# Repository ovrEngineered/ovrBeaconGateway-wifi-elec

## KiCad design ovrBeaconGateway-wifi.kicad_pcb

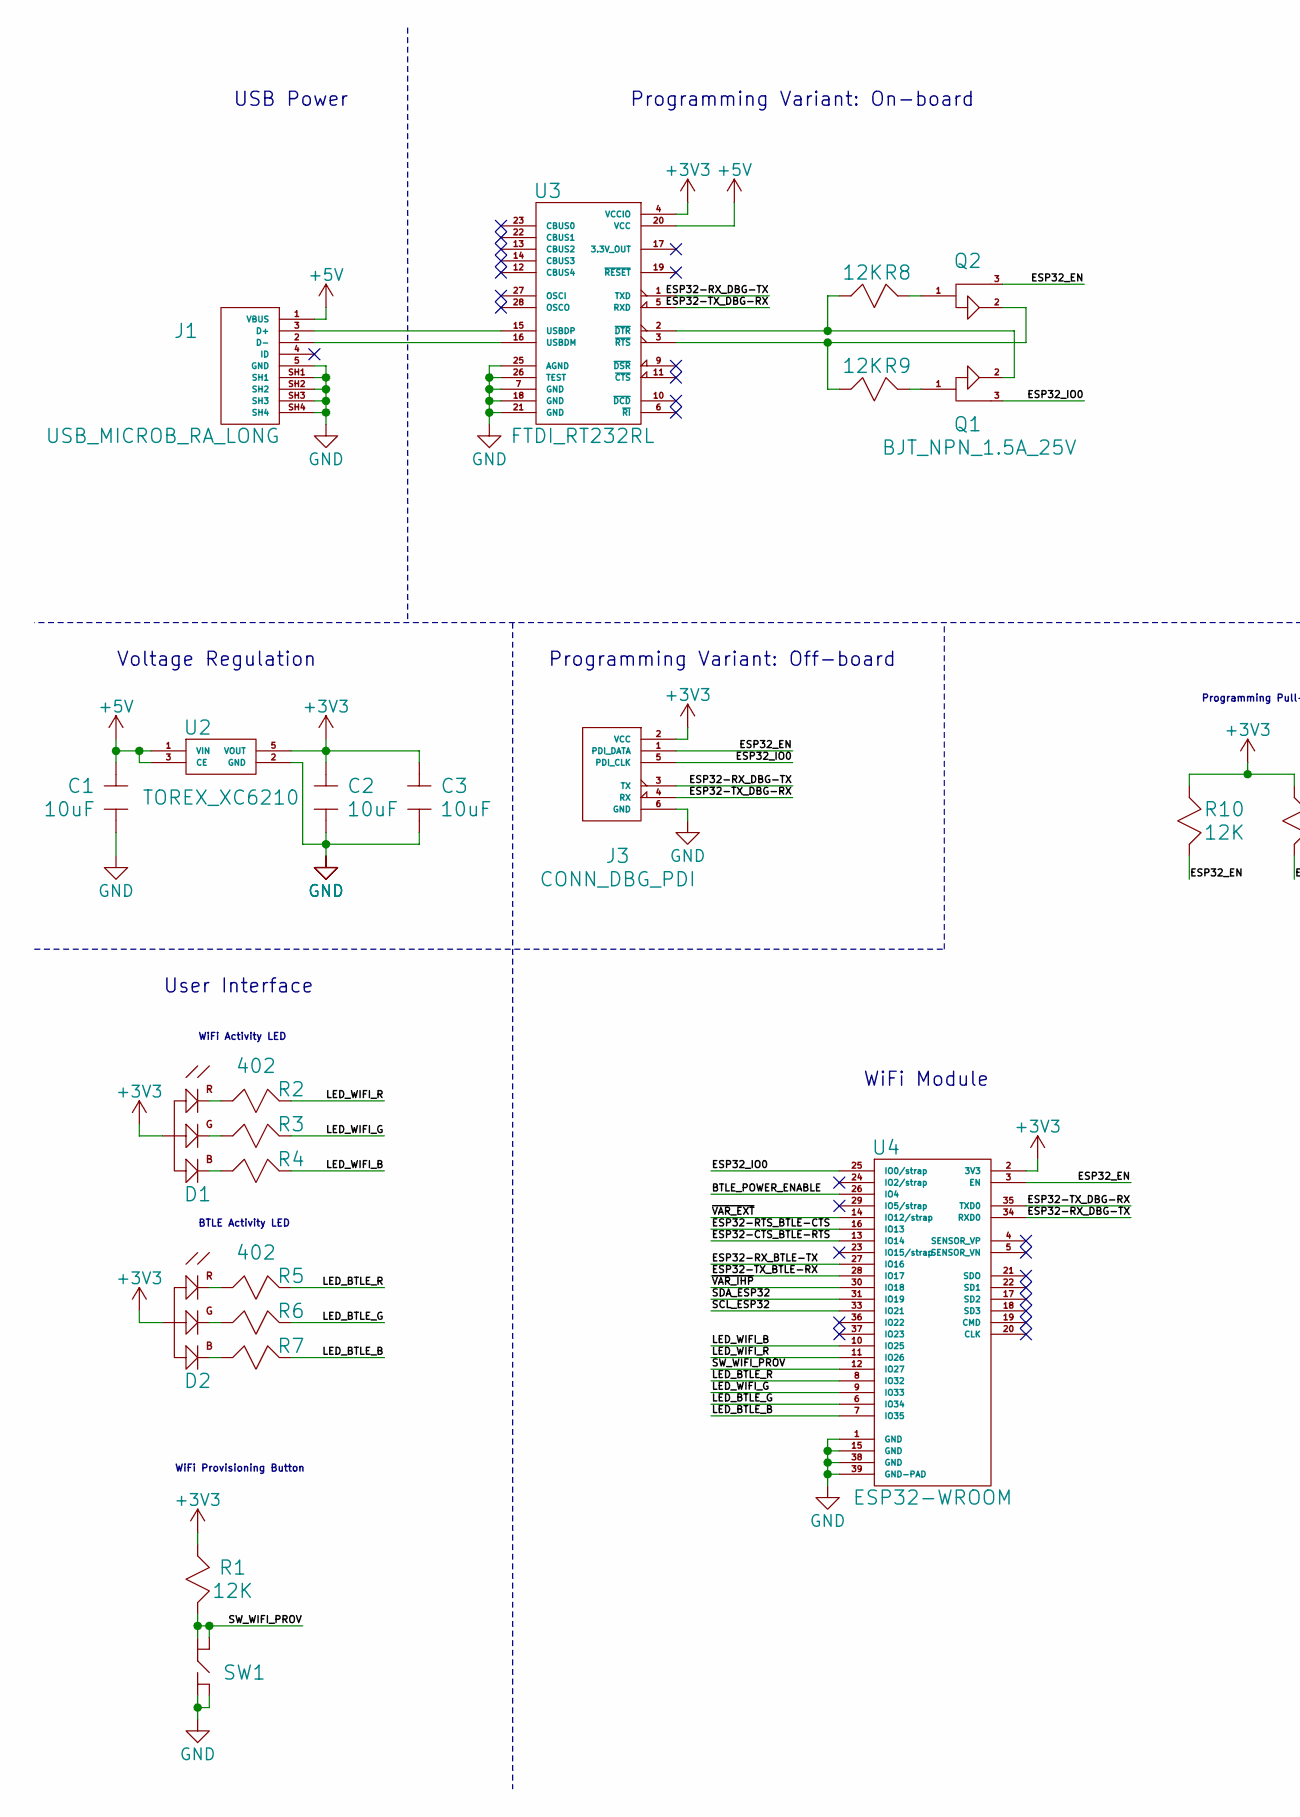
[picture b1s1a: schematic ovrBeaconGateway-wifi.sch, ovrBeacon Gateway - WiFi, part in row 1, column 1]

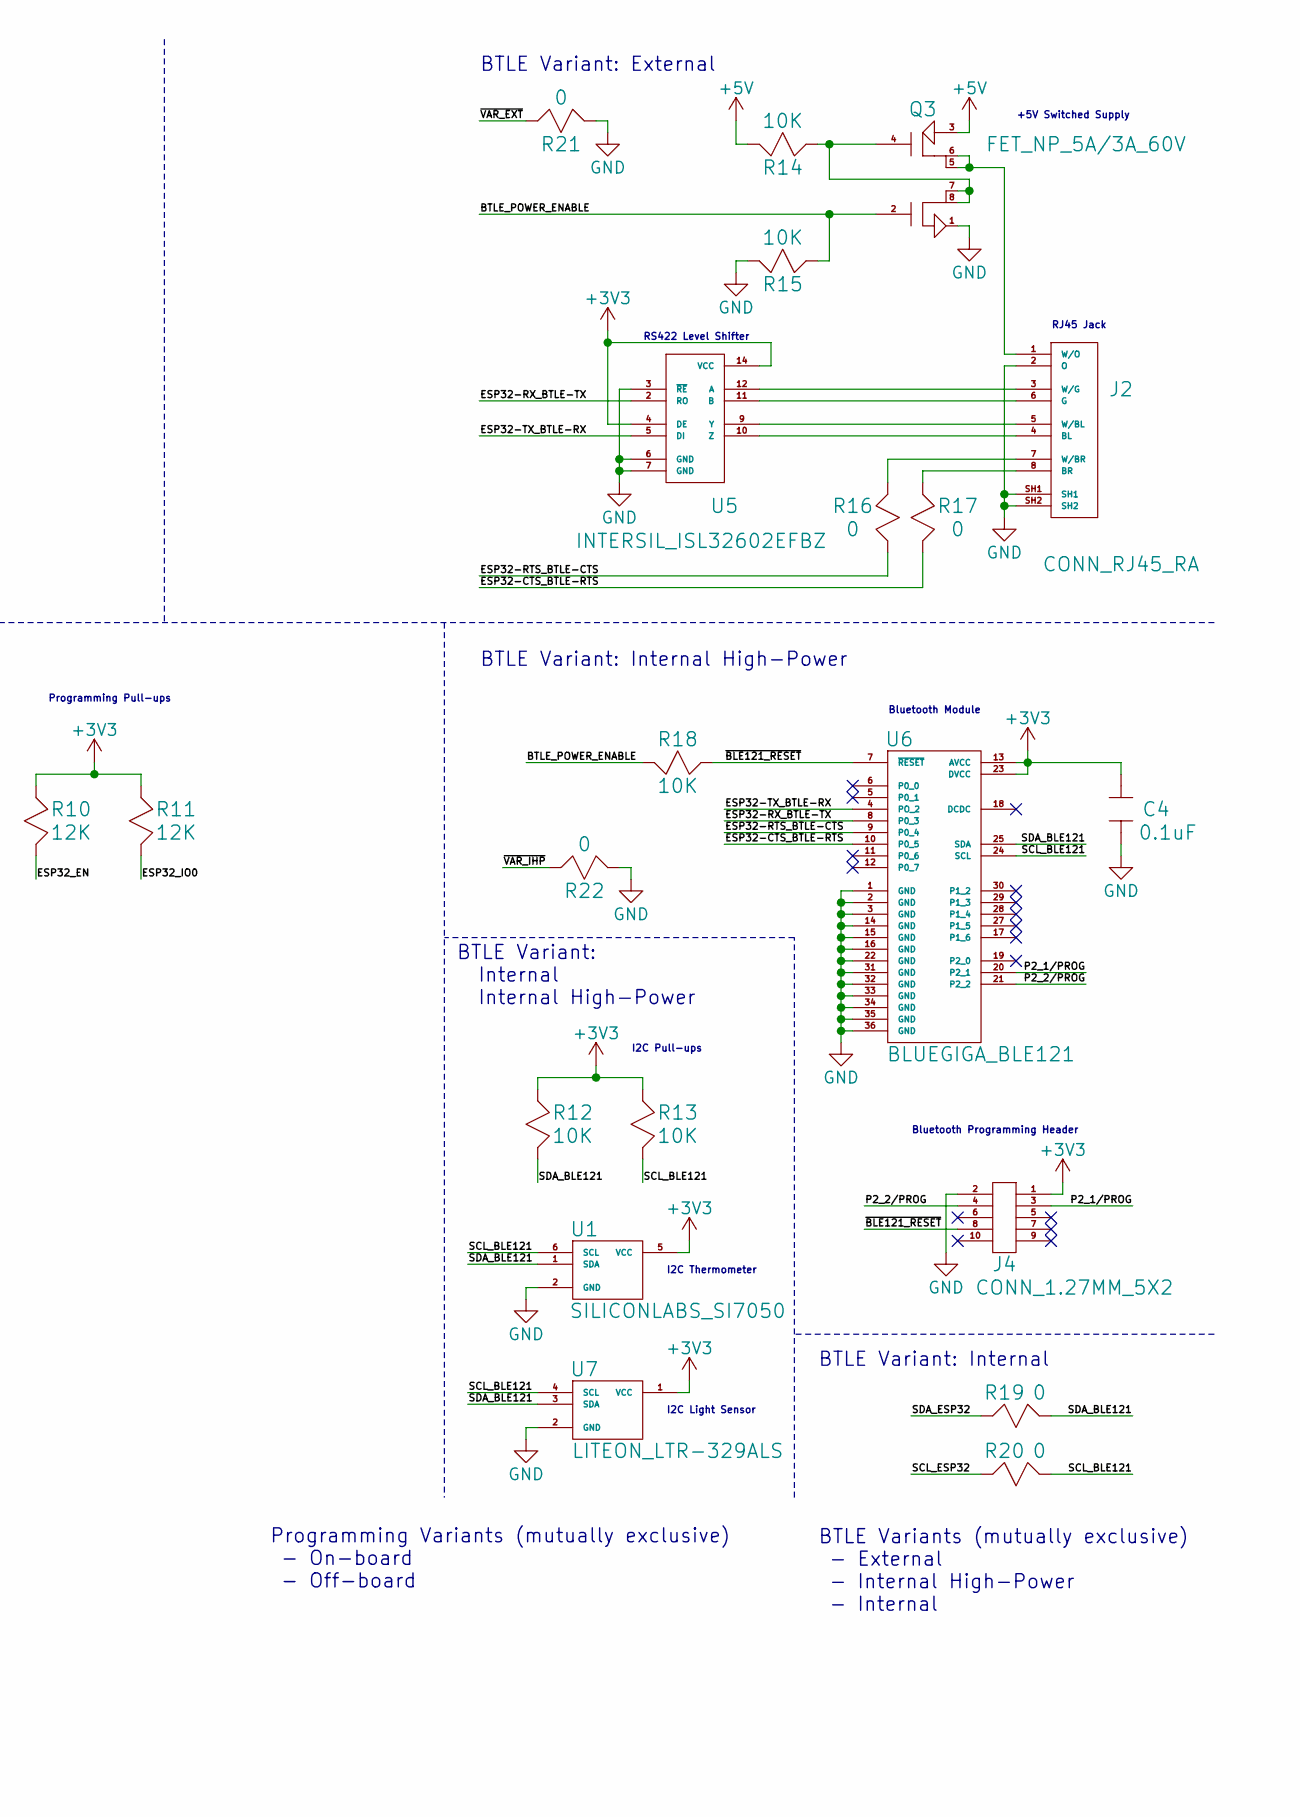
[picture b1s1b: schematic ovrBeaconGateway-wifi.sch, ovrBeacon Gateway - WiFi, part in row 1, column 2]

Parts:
C1, C2, C3: C_10uF_10v_0805; C_0805; Man. Part Num. GRM21BR71A106KE51L
C4: C_0.1uF_10v_0603; C_0603; Man. Part Num. GRM188R71C104KA01D
D1, D2: CREE_CLV1A_FKB; Man. Part Num. CLV1A-FKB-CK1N1G1BB7R4S3
J1: USB_MICROB_RA_LONG; UJ2-MIBH-4-SMT; Man. Part Num. UJ2-MIBH-4-SMT
J2: CONN_RJ45_RA; RJ45_NOMAG_RA; Man. Part Num. E6588-52L184-L
J3: CONN_DBG_PDI; TC2030-IDC; Man. Part Num. TC2030-IDC
J4: CONN_1.27MM_5X2; 20021111-00010T4LF; Man. Part Num. 20021111-00010T4LF
Q1, Q2: BJT_NPN_1.5A_25V; SOT-23-3; Man. Part Num. MMSS8050-H-TP
Q3: FET_NP_5A/3A_60V; SO-8; Man. Part Num. DMC6040SSD-13
R1, R8, R9, R10, R11: R_12K_1%_0603; R_0603; Man. Part Num. CRCW060312K0FKEA
R2, R3, R4, R5, R6, R7: R_402_1%_0603; R_0603; Man. Part Num. CRCW0603402RFKEA
R12, R13, R14, R15, R18: R_10K_1%_0603; R_0603; Man. Part Num. CRCW060310K0FKEA
R16, R17, R19, R20, R21, R22: R_0_0603; R_0603; Man. Part Num. CRCW06030000Z0EA
SW1: ESWITCH_TL3315NF100Q; TL3315NF100Q; Man. Part Num. TL3315NF100Q
U1: SILICONLABS_SI7050; Man. Part Num. SI7050-A20-IM
U2: TOREX_XC6210; SOT-25-5; Man. Part Num. XC6210B332MR-G
U3: FTDI_RT232RL; FT232RL; Man. Part Num. FT232RL
U4: ESP32-WROOM; Man. Part Num. esp-wroom-32
U5: INTERSIL_ISL32602EFBZ; SOIC-14; Man. Part Num. ISL32602EFBZ
U6: BLUEGIGA_BLE121; BLE121; Man. Part Num. BLE121LR-A-M256K
U7: LITEON_LTR-329ALS; Man. Part Num. LTR-329ALS-01

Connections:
+3V3: C2.1, C3.1, C4.1, D1.2 (ANODE), D2.2 (ANODE), J3.2 (VCC), J4.1, R1.1, R10.1, R11.1, R12.1, R13.1, U1.5 (VCC), U2.5 (VOUT), U3.4 (VCCIO), U4.2 (3V3), U5.4 (DE), U5.14 (VCC), U6.13 (AVCC), U6.23 (DVCC), U7.1 (VCC)
+5V: C1.1, J1.1 (VBUS), Q3.3, R14.2, U2.1 (VIN), U2.3 (CE), U3.20 (VCC)
/BTLE_POWER_ENABLE: Q3.2, R15.1, R18.2, U4.26 (IO4)
/ESP32-CTS_BTLE-RTS: R17.2, U4.13 (IO14), U6.10 (P0_5)
/ESP32-RTS_BTLE-CTS: R16.2, U4.16 (IO13), U6.9 (P0_4)
/ESP32-RX_BTLE-TX: U4.27 (IO16), U5.2 (RO), U6.8 (P0_3)
/ESP32-RX_DBG-TX: J3.3 (TX), U3.1 (TXD), U4.34 (RXD0)
/ESP32-TX_BTLE-RX: U4.28 (IO17), U5.5 (DI), U6.4 (PO_2)
/ESP32-TX_DBG-RX: J3.4 (RX), U3.5 (RXD), U4.35 (TXD0)
/ESP32_EN: J3.1 (PDI_DATA), Q2.3, R10.2, U4.3 (EN)
/ESP32_IO0: J3.5 (PDI_CLK), Q1.3, R11.2, U4.25 (IO0/strap)
/LED_BTLE_B: R7.2, U4.7 (IO35)
/LED_BTLE_G: R6.2, U4.6 (IO34)
/LED_BTLE_R: R5.2, U4.8 (IO32)
/LED_WIFI_B: R4.2, U4.10 (IO25)
/LED_WIFI_G: R3.2, U4.9 (IO33)
/LED_WIFI_R: R2.2, U4.11 (IO26)
/P2_1/PROG: J4.3, U6.20 (P2_1)
/P2_2/PROG: J4.4, U6.21 (P2_2)
/SCL_BLE121: R13.2, R20.2, U1.6 (SCL), U6.24 (SCL), U7.4 (SCL)
/SCL_ESP32: R20.1, U4.33 (IO21)
/SDA_BLE121: R12.2, R19.2, U1.1 (SDA), U6.25 (SDA), U7.3 (SDA)
/SDA_ESP32: R19.1, U4.31 (IO19)
/SW_WIFI_PROV: R1.2, SW1.1, SW1.2, U4.12 (IO27)
/~BLE121_RESET: J4.8, R18.1, U6.7 (~RESET)
/~VAR_EXT: R21.1, U4.14 (IO12/strap)
/~VAR_IHP: R22.1, U4.30 (IO18)
GND: C1.2, C2.2, C3.2, C4.2, J1.5 (GND), J1.SH1, J1.SH2, J1.SH3, J1.SH4, J2.2 (O), J2.SH1, J2.SH2, J3.6 (GND), J4.2, Q3.1, R15.2, R21.2, R22.2, SW1.3, SW1.4, U1.2 (GND), U2.2 (GND), U3.7 (GND), U3.18 (GND), U3.21 (GND), U3.25 (AGND), U3.26 (TEST), U4.1 (GND), U4.15 (GND), U4.38 (GND), U4.39 (GND-PAD), U5.3 (~RE), U5.6 (GND), U5.7 (GND), U6.1 (GND), U6.2 (GND), U6.3 (GND), U6.14 (GND), U6.15 (GND), U6.16 (GND), U6.22 (GND), U6.31 (GND), U6.32 (GND), U6.33 (GND), U6.34 (GND), U6.35 (GND), U6.36 (GND), U7.2 (GND)
unnamed: D1.1 (CATHODE_RED), R2.1
unnamed: D1.3 (CATHODE_BLUE), R4.1
unnamed: D1.4 (CATHOD_GREEN), R3.1
unnamed: D2.1 (CATHODE_RED), R5.1
unnamed: D2.3 (CATHODE_BLUE), R7.1
unnamed: D2.4 (CATHOD_GREEN), R6.1
unnamed: J1.2 (D-), U3.16 (USBDM)
unnamed: J1.3 (D+), U3.15 (USBDP)
unnamed: J2.1 (W/O), Q3.5, Q3.6
unnamed: J2.3 (W/G), U5.12 (A)
unnamed: J2.4 (BL), U5.10 (Z)
unnamed: J2.5 (W/BL), U5.9 (Y)
unnamed: J2.6 (G), U5.11 (B)
unnamed: J2.7 (W/BR), R16.1
unnamed: J2.8 (BR), R17.1
unnamed: Q1.1, R9.2
unnamed: Q1.2, R8.1, U3.2 (~DTR)
unnamed: Q2.1, R8.2
unnamed: Q2.2, R9.1, U3.3 (~RTS)
unnamed: Q3.4, Q3.7, Q3.8, R14.1

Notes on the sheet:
USB Power
BTLE Variant: External
Voltage Regulation
WiFi Module
BTLE Variant: Internal High-Power
Programming Variant: Off-board
Programming Variant: On-board
+5V Switched Supply
BTLE Variants (mutually exclusive) - External - Internal High-Power - Internal
RS422 Level Shifter
RJ45 Jack
Bluetooth Module
Bluetooth Programming Header
I2C Thermometer
BTLE Variant: Internal
Programming Variants (mutually exclusive) - On-board - Off-board
Programming Pull-ups
BTLE Variant: Internal Internal High-Power
I2C Light Sensor
I2C Pull-ups
WiFi Activity LED
BTLE Activity LED
WiFi Provisioning Button
User Interface

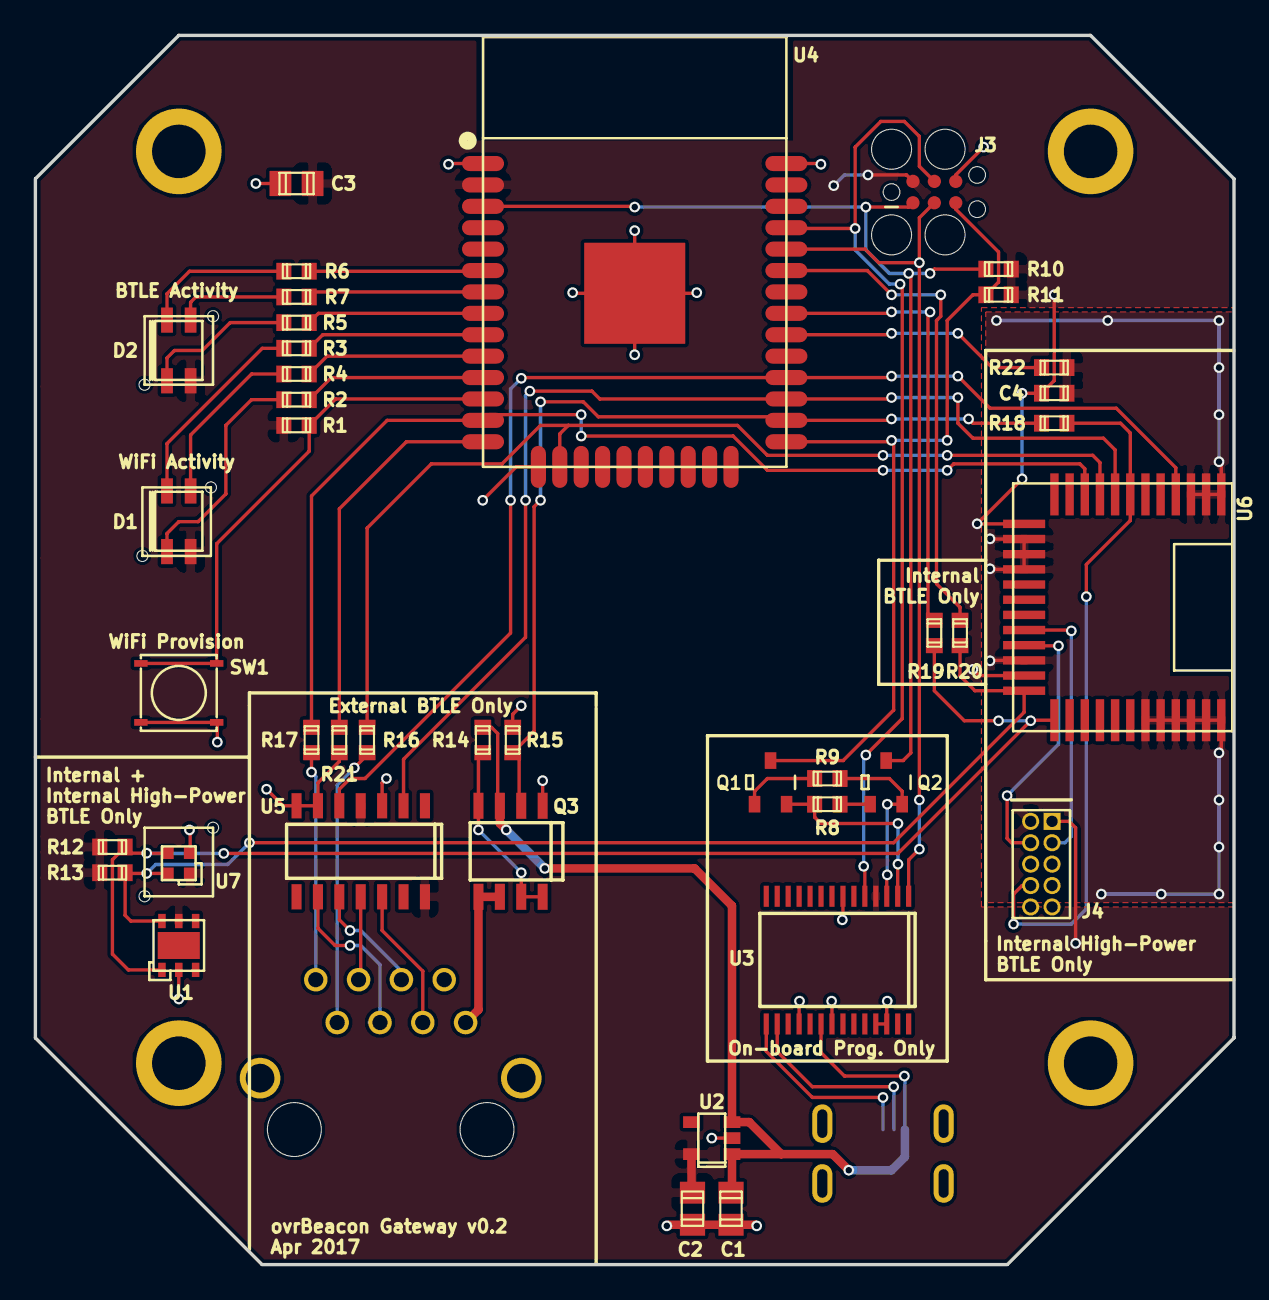
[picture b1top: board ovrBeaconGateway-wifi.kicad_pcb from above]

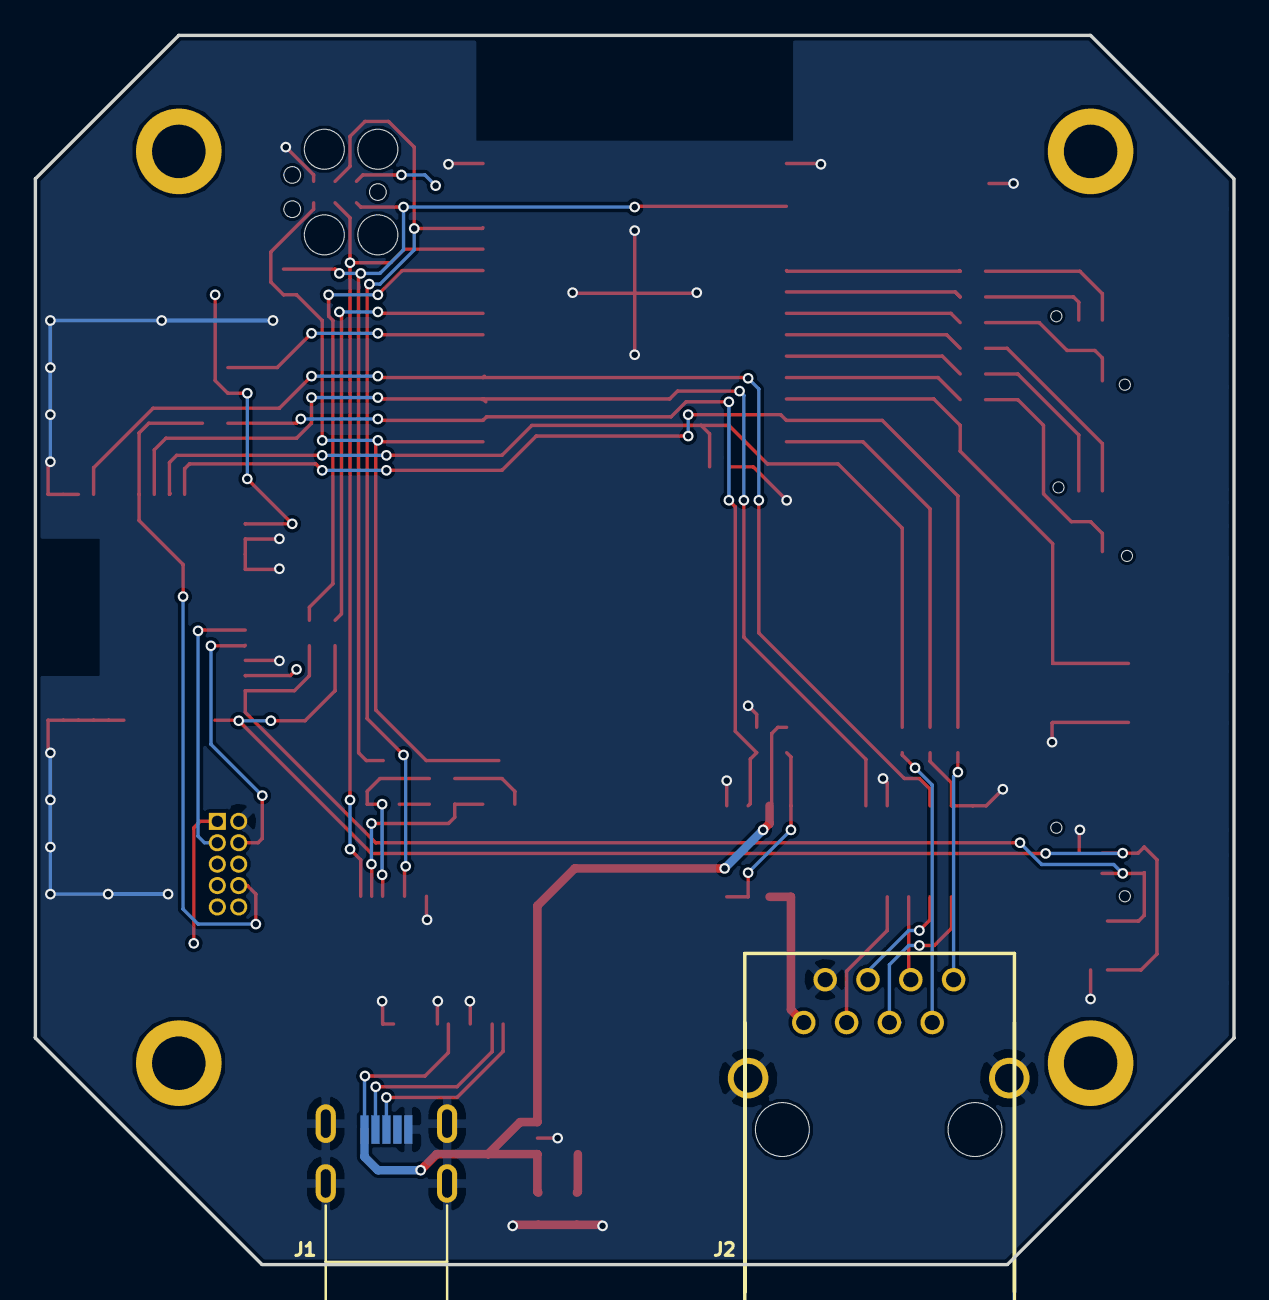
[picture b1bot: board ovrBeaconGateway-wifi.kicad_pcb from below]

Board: 2 copper layers, 71.1 x 72.9 mm, 43 parts (2 on the bottom side), 48 nets.

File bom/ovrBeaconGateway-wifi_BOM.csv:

Reference,Value,Footprint,Datasheet,Manufacturer,Man. Part Num.,Supplier,Supplier Part Num.,Comp. Value,Quantity
J2,CONN_RJ45_RA,ovrEngineered:RJ45_NOMAG_RA,http://productfinder.pulseeng.com/products/datasheets/E6588-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,Pulse Electronics,E6588-52L184-L,Digi-Key,553-2265-ND,,1
U2,TOREX_XC6210,ovrEngineered:SOT-25-5,https://www.torexsemi.com/file/xc6210/XC6210.pdf,Torex Semiconductor,XC6210B332MR-G,Digi-Key,893-1075-1-ND,,1
U1,SILICONLABS_SI7050,ovrEngineered:SILICONLABS_SI7050,http://www.silabs.com/Support%20Documents/TechnicalDocs/Si70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,Silicon Labs,SI7050-A20-IM,Digi-Key,336-3118-5-ND,,1
U5,INTERSIL_ISL32602EFBZ,ovrEngineered:SOIC-14,http://www.intersil.com/content/dam/Intersil/documents/fn79/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,Intersil,ISL32602EFBZ,Digi-Key,ISL32602EFBZ-ND,,1
U3,FTDI_RT232RL,ovrEngineered:FT232RL,http://www.ftdichip.com/Support/Documents/DataSheets/ICs/DS_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,FTDI,FT232RL,Digi-Key,768-1007-1-ND,,1
R8 R9 R10 R11 R1,R_12K_1%_0603,ovrEngineered:R_0603,http://www.vishay.com/docs/20035/dcrcwe3.pdf,Vishay_Dale,CRCW060312K0FKEA,Digi-Key,541-12.0KHCT-ND,12K,5
C1 C2 C3,C_10uF_10v_0805,ovrEngineered:C_0805,http://psearch.murata.com/capacitor/product/GRM21BR71A106KE5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,Murata,GRM21BR71A106KE51L,Digi-Key,490-3905-1-ND,10uF,3
Q3,FET_NP_5A/3A_60V,ovrEngineered:SO-8,http://diodes.com/datasheets/DMC6040SSD.pdf,International Rectifier,DMC6040SSD-13,Digi-Key,DMC6040SSD-13DICT-ND,,1
R15 R14 R18 R12 R13,R_10K_1%_0603,ovrEngineered:R_0603,http://www.vishay.com/docs/20035/dcrcwe3.pdf,Vishay_Dale,CRCW060310K0FKEA,Digi-Key,541-10.0KHCT-ND,10K,5
R17 R16 R19 R20 R22 R21,R_0_0603,ovrEngineered:R_0603,http://www.vishay.com/docs/20035/dcrcwe3.pdf,Vishay_Dale,CRCW06030000Z0EA,Digi-Key,541-0.0GCT-ND,0,6
Q1 Q2,BJT_NPN_1.5A_25V,ovrEngineered:SOT-23-3,http://www.mccsemi.com/up_pdf/MMSS8050(SOT-23).pdf,Micro Commercial Co,MMSS8050-H-TP,Digi-Key,MMSS8050-H-TPMSCT-ND,,2
J1,USB_MICROB_RA_LONG,ovrEngineered:UJ2-MIBH-4-SMT,http://www.cui.com/product/resource/digikeypdf/uj2-mibh-4-smt.pdf,CUI,UJ2-MIBH-4-SMT,Digi-Key,102-4006-1-ND,,1
U6,BLUEGIGA_BLE121,ovrEngineered:BLE121,http://media.digikey.com/pdf/Data%20Sheets/BlueGiga%20PDFs/B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,BlueGiga,BLE121LR-A-M256K,Digi-Key,1446-1039-1-ND,,1
C4,C_0.1uF_10v_0603,ovrEngineered:C_0603,http://search.murata.co.jp/Ceramy/image/img/A01X/G101/ENG/GR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,Murata,GRM188R71C104KA01D,Digi-Key,490-1532-1-ND,0.1uF,1
J4,CONN_1.27MM_5X2,ovrEngineered:20021111-00010T4LF,http://portal.fciconnect.com/Comergent//fci/drawing/20021111.pdf,Amphenol,20021111-00010T4LF,Digi-Key,609-3712-ND,,1
U7,LITEON_LTR-329ALS,ovrEngineered:LITEON_LTR-329ALS,http://optoelectronics.liteon.com/upload/download/DS86-2014-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,Lite-On,LTR-329ALS-01,Digi-Key,160-2160-1-ND,,1
D1 D2,CREE_CLV1A_FKB,ovrEngineered:CREE_CLV1A_FKB,http://media.digikey.com/pdf/Data%20Sheets/CREE%20Power/CLV1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,Cree Inc.,CLV1A-FKB-CK1N1G1BB7R4S3,Digi-Key,CLV1A-FKB-CK1N1G1BB7R4S3CT-ND,RGB,2
R2 R3 R4 R5 R6 R7,R_402_1%_0603,ovrEngineered:R_0603,http://www.vishay.com/docs/20035/dcrcwe3.pdf,Vishay_Dale,CRCW0603402RFKEA,Digi-Key,541-402HCT-ND,402,6
SW1,ESWITCH_TL3315NF100Q,ovrEngineered:TL3315NF100Q,http://spec_sheets.e-switch.com/specs/P010336.pdf,E-Switch,TL3315NF100Q,Digi-Key,EG4620CT-ND,,1
U4,ESP32-WROOM,ovrEngineered:ESP32-WROOM,https://espressif.com/sites/default/files/documentation/esp_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,EspressIf,esp-wroom-32,Grid Connect,GC-ESP-WROOM-32,,1

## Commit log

2017-02-18 Moved BOM added current pricing, ready for manufacture
2017-02-24 Included an optional BLE121 on this module to allow for stand-alone long range operation
2017-02-24 Updated BOM and pricing…still waiting for quote on BLE121
2017-02-26 Added PDF schematic
2017-02-26 Added layout pdf
2017-02-26 Added price for BLE121
2017-03-07 Updated pricing document w/ variants
2017-04-24 Initial commit of second revision changes
2017-04-25 updated BOM
2017-04-25 Fixed field offset and removed tag-connect programming port
2017-05-01 Out for DFM
2017-05-01 Added schematic and layout
